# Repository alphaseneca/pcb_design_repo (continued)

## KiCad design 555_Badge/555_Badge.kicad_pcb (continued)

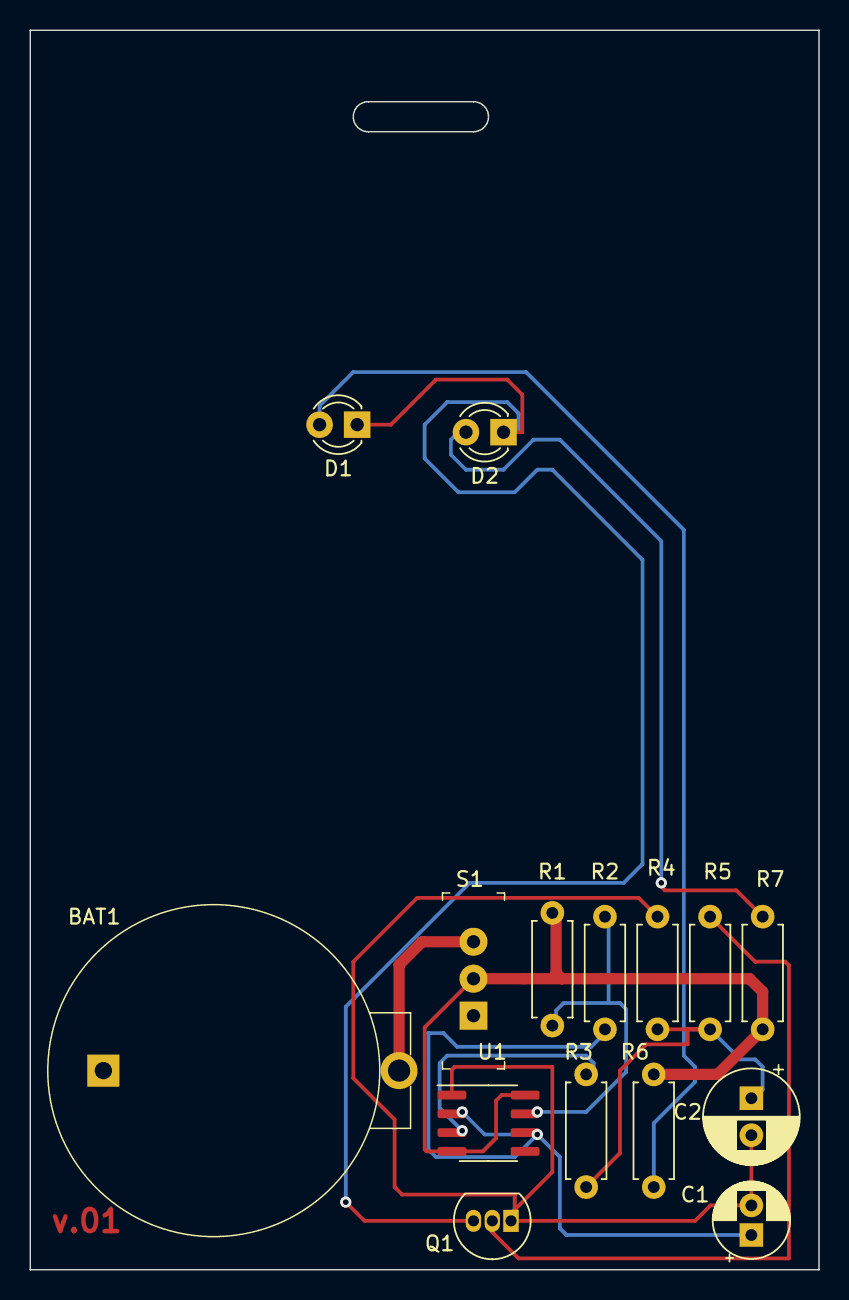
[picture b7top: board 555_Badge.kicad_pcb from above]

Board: 2 copper layers, 53.3 x 83.8 mm, 15 parts (0 on the bottom side), 11 nets.

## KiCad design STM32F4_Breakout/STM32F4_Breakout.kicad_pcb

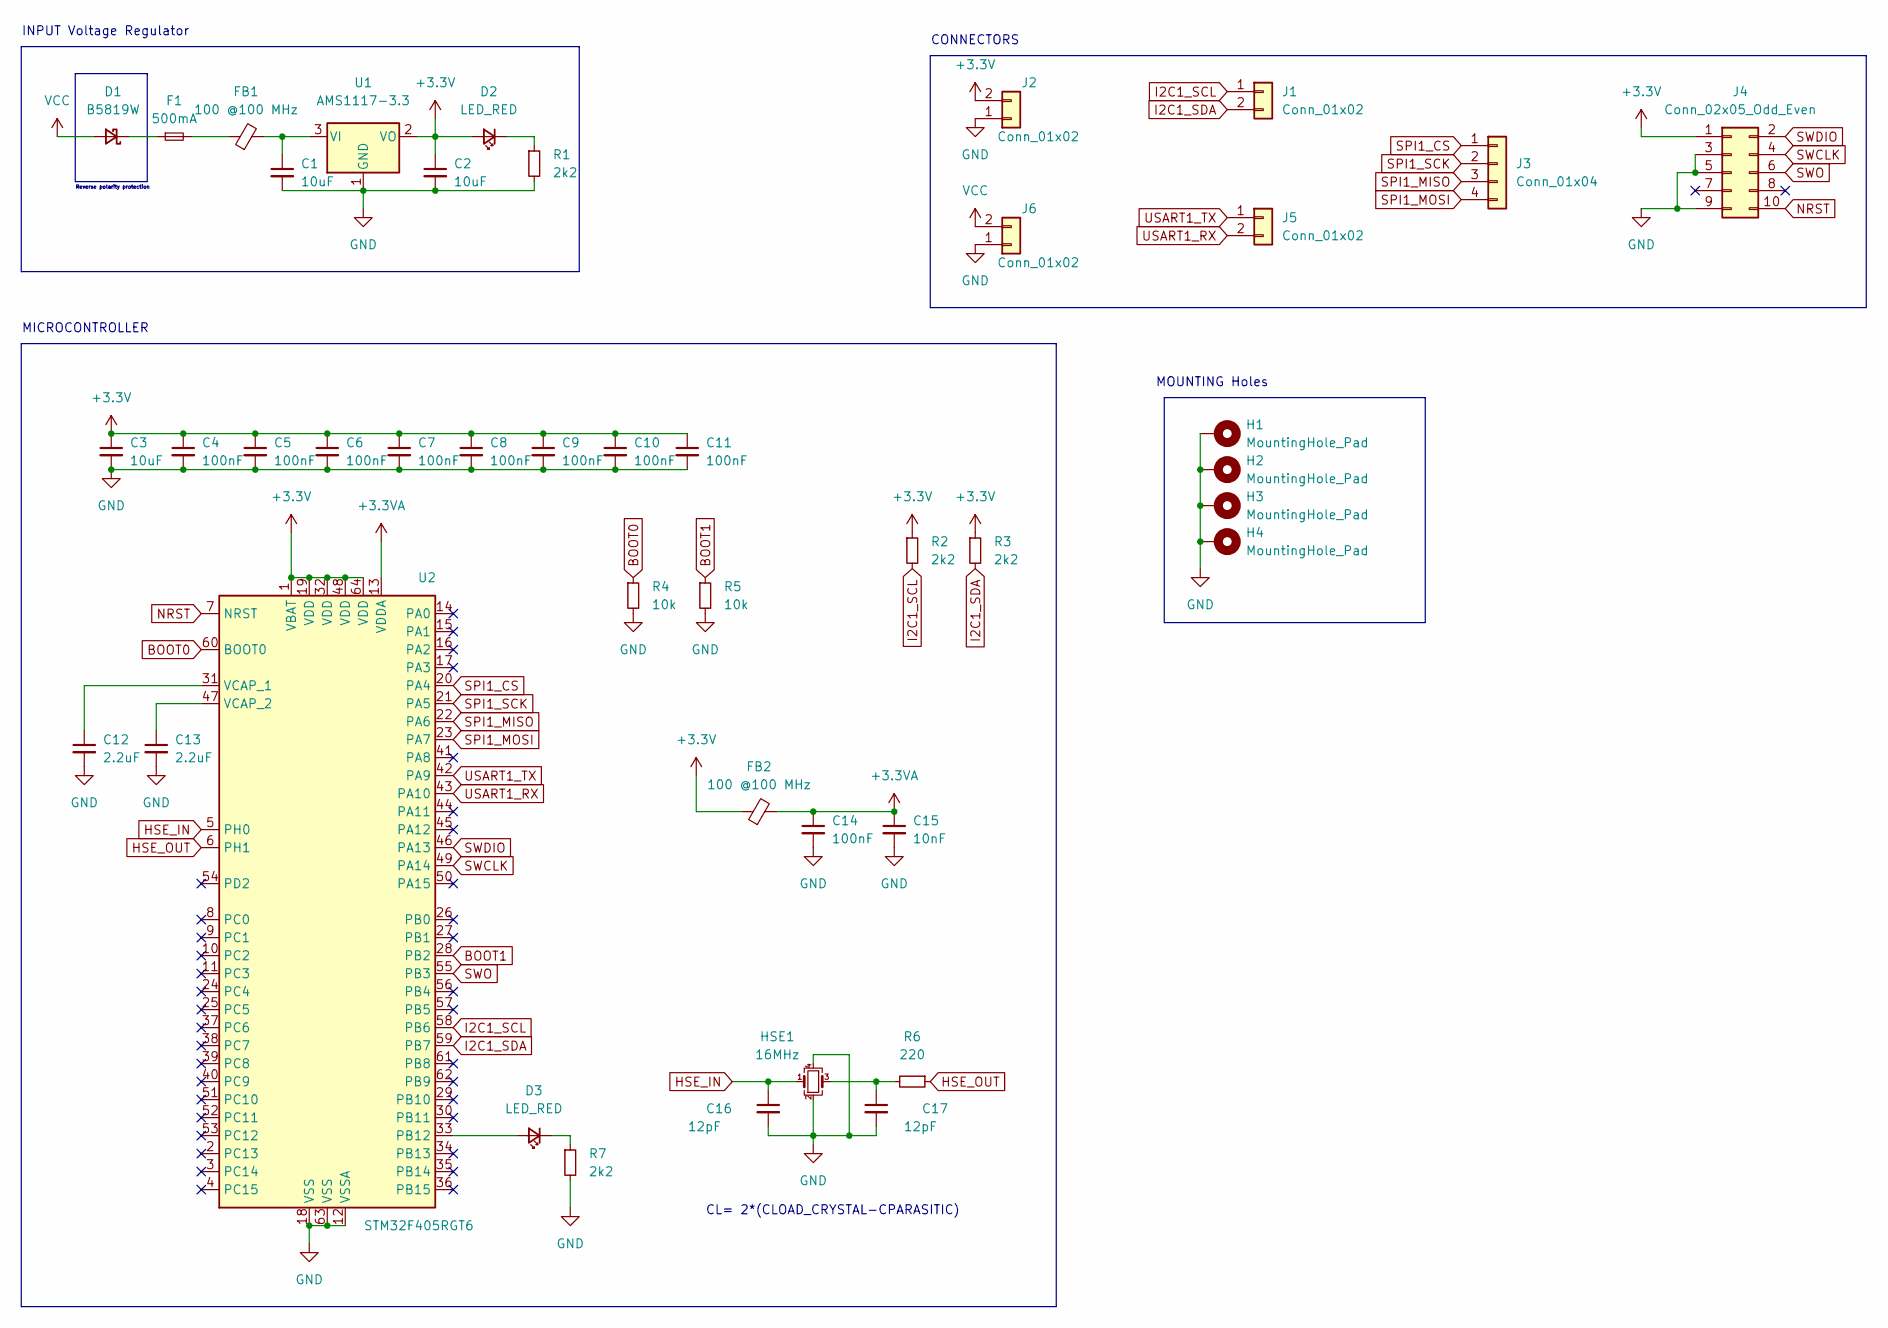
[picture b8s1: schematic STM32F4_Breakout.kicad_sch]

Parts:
C1, C2: 10uF; C_0805_2012Metric
C3: 10uF; C_0603_1608Metric
C4, C5, C6, C7, C8, C9, C10, C11, C14: 100nF; C_0402_1005Metric
C12, C13: 2.2uF; C_0603_1608Metric
C15: 10nF; C_0402_1005Metric
C16, C17: 12pF; C_0402_1005Metric
D1: B5819W; D_SOD-123
D2, D3: LED_RED; LED_0201_0603Metric
F1: 500mA; Fuse_0603_1608Metric
FB1, FB2: 100 @100 MHz; L_0805_2012Metric
H1, H2, H3, H4: MountingHole_Pad; MountingHole_4.3mm_M4_Pad_Via
HSE1: 16MHz; Crystal_SMD_3225-4Pin_3.2x2.5mm
J1, J2, J5, J6: Conn_01x02; PinHeader_1x02_P2.54mm_Vertical
J3: Conn_01x04; PinHeader_1x04_P2.54mm_Vertical
J4: Conn_02x05_Odd_Even; PinHeader_2x05_P1.27mm_Vertical_SMD
R1, R7: 2k2; R_0603_1608Metric
R2, R3: 2k2; R_0402_1005Metric
R4, R5: 10k; R_0402_1005Metric
R6: 220; R_0402_1005Metric
U1: AMS1117-3.3; SOT-223-3_TabPin2
U2: STM32F405RGT6; LQFP-64_10x10mm_P0.5mm

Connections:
+3.3VA: C14.1, C15.1, FB2.2, U2.13 (VDDA)
+3V3: C2.1, C3.1, C4.1, C5.1, C6.1, C7.1, C8.1, C9.1, C10.1, C11.1, D2.2 (A), FB2.1, J2.2, J4.1, R2.1, R3.1, U1.2 (VO), U2.1 (VBAT), U2.19 (VDD), U2.32 (VDD), U2.48 (VDD), U2.64 (VDD)
BOOT0: R4.1, U2.60 (BOOT0)
BOOT1: R5.1, U2.28 (PB2)
GND: C1.2, C2.2, C3.2, C4.2, C5.2, C6.2, C7.2, C8.2, C9.2, C10.2, C11.2, C12.2, C13.2, C14.2, C15.2, C16.2, C17.2, H1.1, H2.1, H3.1, H4.1, HSE1.2, HSE1.4, J2.1, J4.3, J4.5, J4.9, J6.1, R1.2, R4.2, R5.2, R7.2, U1.1 (GND), U2.12 (VSSA), U2.18 (VSS), U2.63 (VSS)
HSE_IN: C16.1, HSE1.1, U2.5 (PH0)
HSE_OUT: R6.1, U2.6 (PH1)
I2C1_SCL: J1.1, R2.2, U2.58 (PB6)
I2C1_SDA: J1.2, R3.2, U2.59 (PB7)
NRST: J4.10, U2.7 (NRST)
unnamed: C1.1, FB1.2, U1.3 (VI)
unnamed: C12.1, U2.31 (VCAP_1)
unnamed: C13.1, U2.47 (VCAP_2)
unnamed: C17.1, HSE1.3, R6.2
unnamed: D1.1 (K), F1.1
unnamed: D2.1 (K), R1.1
unnamed: D3.1 (K), R7.1
unnamed: D3.2 (A), U2.33 (PB12)
unnamed: F1.2, FB1.1
SPI1_CS: J3.1, U2.20 (PA4)
SPI1_MISO: J3.3, U2.22 (PA6)
SPI1_MOSI: J3.4, U2.23 (PA7)
SPI1_SCK: J3.2, U2.21 (PA5)
SWCLK: J4.4, U2.49 (PA14)
SWDIO: J4.2, U2.46 (PA13)
SWO: J4.6, U2.55 (PB3)
USART1_RX: J5.2, U2.43 (PA10)
USART1_TX: J5.1, U2.42 (PA9)
VCC: D1.2 (A), J6.2

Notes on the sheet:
INPUT Voltage Regulator
CL= 2*(CLOAD_CRYSTAL-CPARASITIC)
CONNECTORS
MOUNTING Holes
Reverse polarity protection
MICROCONTROLLER

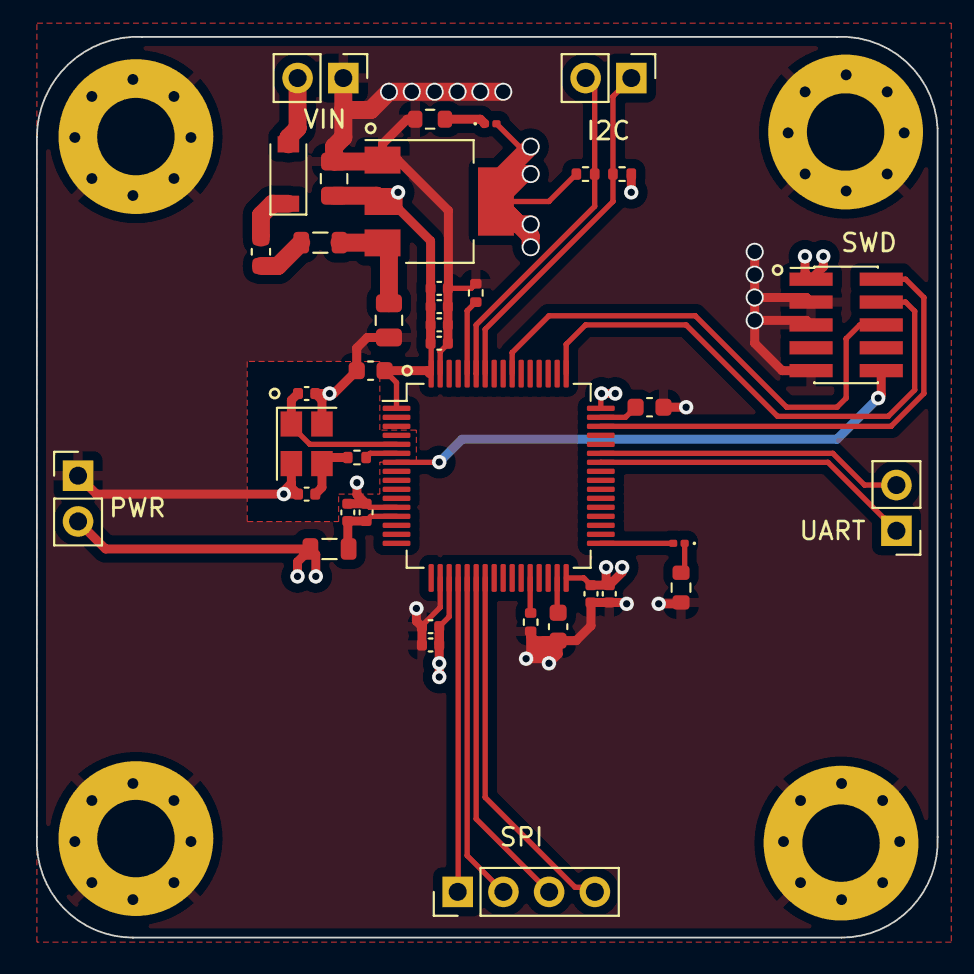
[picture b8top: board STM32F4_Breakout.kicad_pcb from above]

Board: 4 copper layers, 50.0 x 50.0 mm, 43 parts (0 on the bottom side), 29 nets.

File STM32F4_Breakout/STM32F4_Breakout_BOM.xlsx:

Designator | Quantity | Value | Footprint | LCSC Part #
C1, C2, | 2 | 10uF | 805 | C15850
C3, | 1 | 10uF | 603 | C19702
C4, C5, C6, C7, C8, C9, C10, C11, C14, | 9 | 100nF | 402 | C1525
C12, C13, | 2 | 2.2uF | 603 | C23630
C15, | 1 | 10nF | 402 | C15195
C16, C17, | 2 | 12pF | 402 | C1547
D1, | 1 | B5819W | SOD-123 | C8598
D2, D3, | 2 | LED_RED | 603 | C2286
F1, | 1 | 500mA | 603
FB1, FB2, | 2 | 100 @100 MHz | 805 | C1015
HSE1, | 1 | 16MHz | SMD_3225-4P | C13178
R1, R7, | 2 | 2k2 | 603 | C4190
R2, R3, | 2 | 2k2 | 402 | C25789
R4, R5, | 2 | 10k | 402 | C25744
R6, | 1 | 220 | 402 | C25091
U1, | 1 | AMS1117-3.3 | SOT-223-3 | C6186
U2, | 1 | STM32F405RGT6 | LQFP-64_10x10mm_P0.5mm | C15742

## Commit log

2024-05-01 Added files
2024-05-02 Added the pcb design files from easyeda export
2024-05-14 Added the stp files for the components and generated footprints for the Filter
2024-05-14 Final schematics and the pcb
2025-04-24 exported images for better visualization
2025-04-24 Added images in the README
